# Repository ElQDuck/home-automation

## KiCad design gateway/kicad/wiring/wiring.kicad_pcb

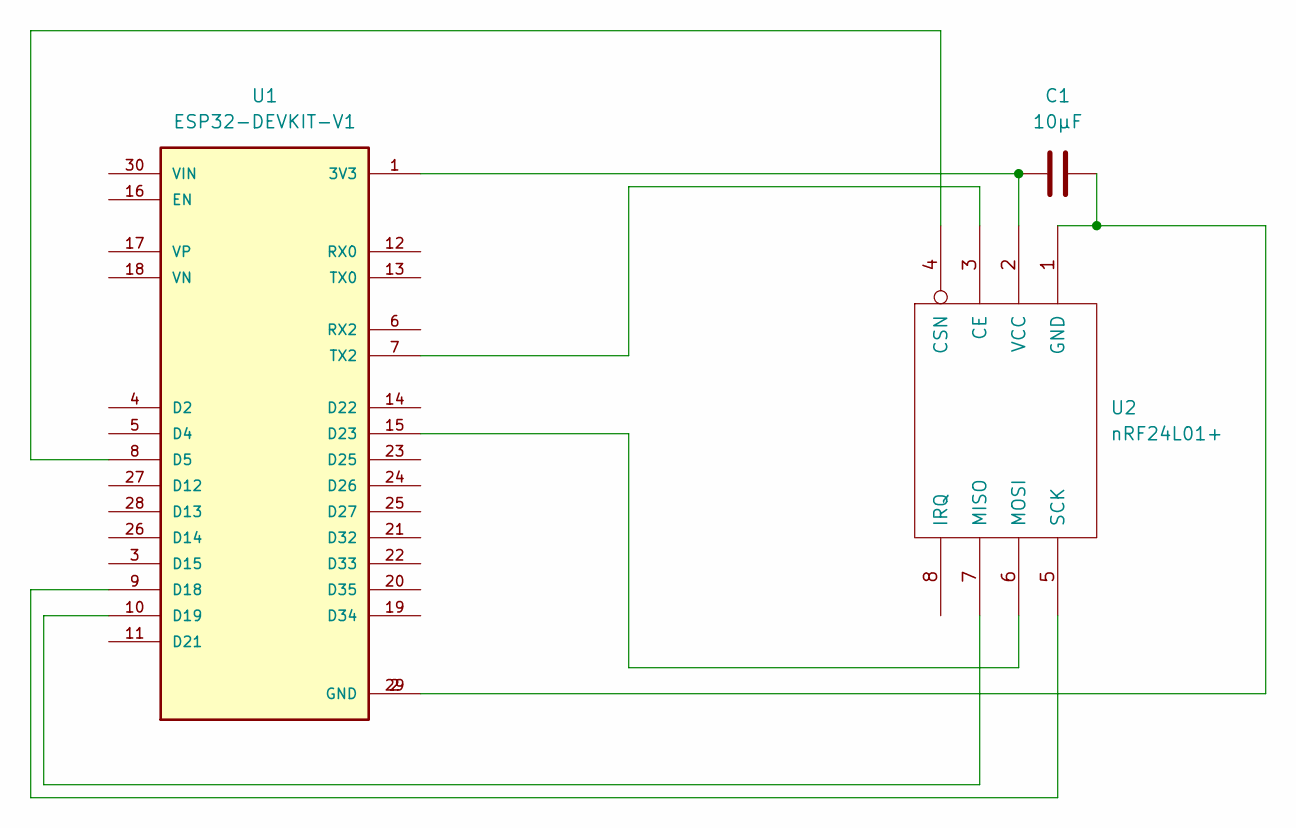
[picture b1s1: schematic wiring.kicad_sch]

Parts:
C1: 10µF; C_Disc_D3.0mm_W1.6mm_P2.50mm
U1: ESP32-DEVKIT-V1; MODULE_ESP32_DEVKIT_V1; PARTREV N/A
U2: nRF24L01+; nRF24L01_Breakout

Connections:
unnamed: C1.1, U1.1 (3V3), U2.2 (VCC)
unnamed: U1.10 (D19), U2.7 (MISO)
unnamed: U1.15 (D23), U2.6 (MOSI)
unnamed: C1.2, U1.2 (GND), U1.29 (GND), U2.1 (GND)
unnamed: U1.7 (TX2), U2.3 (CE)
unnamed: U1.8 (D5), U2.4 (CSN)
unnamed: U1.9 (D18), U2.5 (SCK)

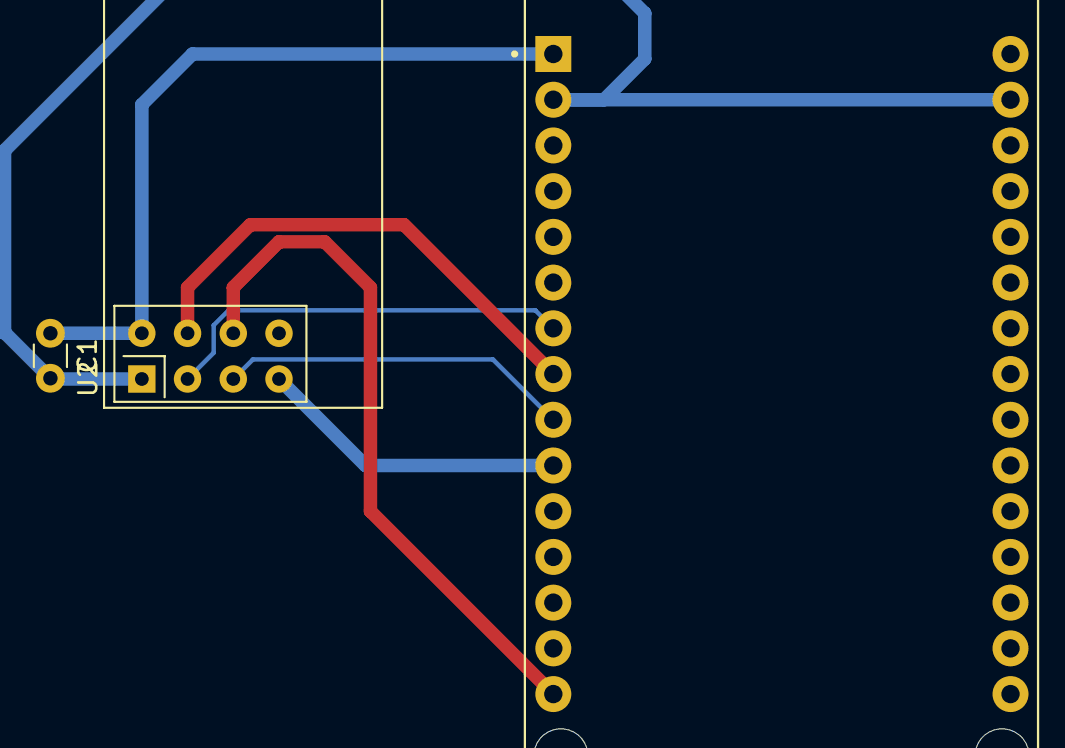
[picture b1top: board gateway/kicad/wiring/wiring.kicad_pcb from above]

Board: 2 copper layers, 3 parts (0 on the bottom side), 7 nets.

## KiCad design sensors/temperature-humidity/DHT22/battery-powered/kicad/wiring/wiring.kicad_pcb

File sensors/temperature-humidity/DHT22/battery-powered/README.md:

# A battery powered temperature and humidity sensor
Used Hardware
- Sensor: [DHT22]()
- Microcontroller: [Arduino Pro Mini ATmega328 3.3V 8MHz ]()
- Wifi connection: [NRF24L01 2.4GHz]()
- Battery: 2 x AA-Battery
- Programmer: [FTDI USB to TTL Serial Adapter](https://www.mikrocontroller.net/topic/435491)
    - [Drivers](https://ftdichip.com/drivers/)

## Development Environment Setup
1. Install [Visual Studio Code](https://code.visualstudio.com/download)
2. Install [PlatformIO IDE](https://marketplace.visualstudio.com/items?itemName=platformio.platformio-ide)
    1. C++ libraries:
        1. [DHT](https://github.com/markruys/arduino-DHT)
        2. [rapidjson](https://github.com/Tencent/rapidjson)
        3. [ArduinoUniqueID](https://github.com/ricaun/ArduinoUniqueID)
        4. [MySensors](https://github.com/mysensors/MySensors/tree/master)
        5. [RF24](https://github.com/nRF24/RF24)
        6. [RF24Network](https://github.com/nRF24/RF24Network)
        7. [arduino-mqtt](https://github.com/256dpi/arduino-mqtt/)
        8. [Low-Power](https://github.com/rocketscream/Low-Power)
        9. [RF24Mesh](https://github.com/nRF24/RF24Mesh)
        10. [RF24Ethernet](https://github.com/nRF24/RF24Ethernet)
4. Install [KiCad]()
    1. [Arduino Libary](https://github.com/Duckle29/kicad-libraries)
    2. [NRF24L01 Library](https://github.com/myelin/myelin-kicad-libraries)
    3. [DHT22 Sensor Library](https://github.com/skorokithakis/kicad-lib.git)
    
    [//]: # (TODO: Move libs into repository)
    
5. (Alternative) install [FreeCAD]()

## Wiring

## Programming
!Attention! After pressing the upload button press the reset button on the Arduino pro mini.

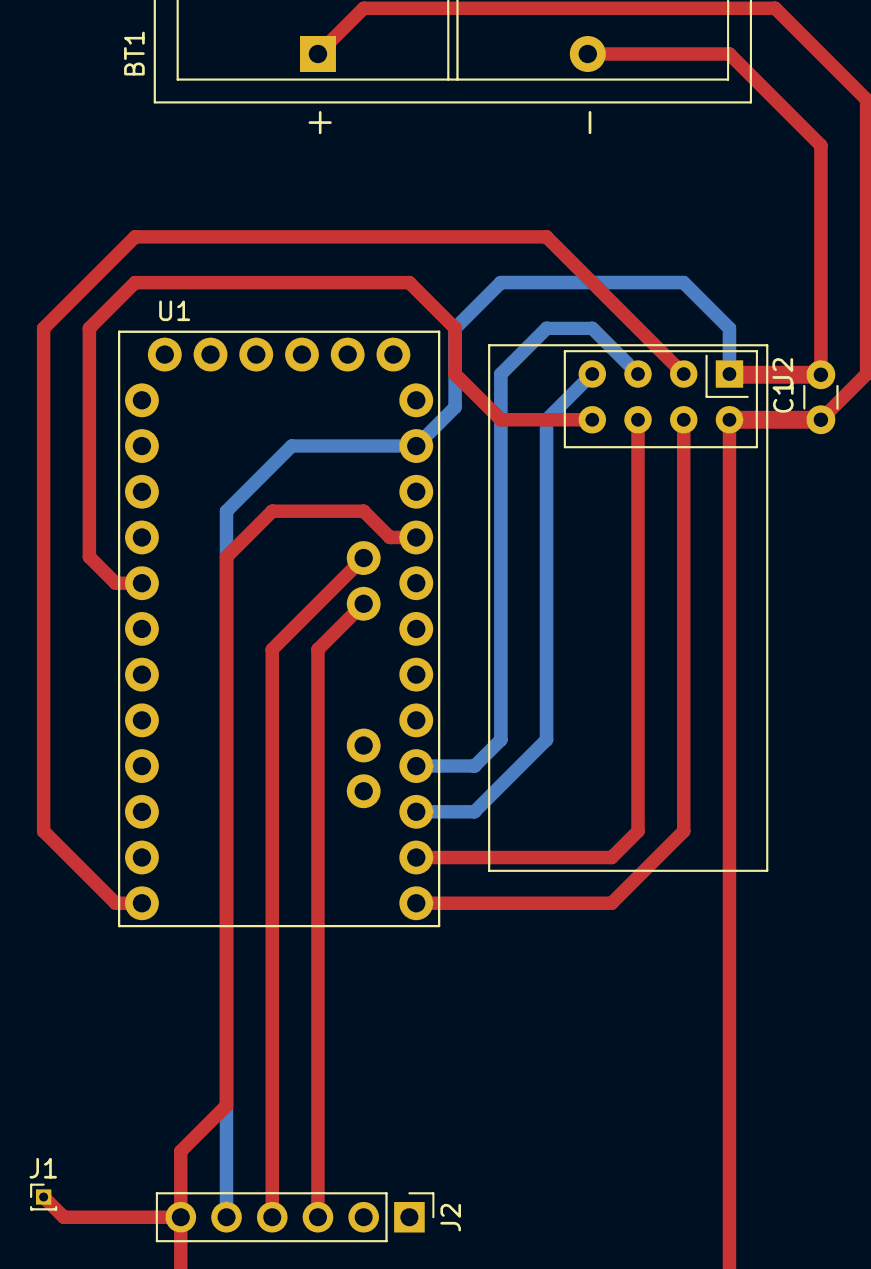
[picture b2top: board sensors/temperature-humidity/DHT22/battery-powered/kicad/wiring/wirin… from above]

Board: 2 copper layers, 6 parts (0 on the bottom side), 11 nets.

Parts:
BT1: 2x1,5V; BatteryHolder_Keystone_2462_2xAA
C1: 10µF; C_Disc_D3.0mm_W1.6mm_P2.50mm
J1: Conn_01x01_Male; PinHeader_1x01_P1.00mm_Vertical
J2: BME280; PinHeader_1x06_P2.54mm_Vertical
U1: ARDUINO_PRO_MINI; MODULE_ARDUINO_PRO_MINI
U2: nRF24L01+; nRF24L01_Breakout

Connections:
GND: BT1.2 (-), C1.2, J2.5, U1.JP6_2 (GND_1), U2.1 (GND)
unnamed: U1.JP1_5 (GND), U1.JP1_6 (GND)
unnamed: J2.3, U1.JP2_1 (A4)
unnamed: J2.4, U1.JP2_2 (A5)
unnamed: BT1.1 (+), C1.1, J1.1, J2.6, U1.JP6_4 (VCC_1), U2.2 (VCC)
unnamed: U1.JP6_9 (SCK), U2.5 (SCK)
unnamed: U1.JP6_10 (MISO), U2.7 (MISO)
unnamed: U1.JP6_11 (MOSI), U2.6 (MOSI)
unnamed: U1.JP6_12 (D10), U2.4 (CSN)
unnamed: U1.JP7_1 (D9), U2.3 (CE)
unnamed: U1.JP7_8 (D2), U2.8 (IRQ)

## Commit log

2022-02-22 feat: adding readme
2022-02-22 feat: new kicad project
2022-02-22 feat: adding library
2022-02-24 feat: using platform io
2022-02-25 feat: add platform io project
2022-02-25 feat: adding libraries to kikad
2022-02-25 feat: adding schematics
2022-02-25 feat: adding mqtt deployment
2022-02-25 refactor: minor changes
2022-02-26 feat: add openhab yaml
2022-03-02 feat: adding first sketch
2022-03-26 feat: adding json creation and arduino id
2022-03-26 feat: adding battery voltage measurement
2022-03-26 feat: using better method to measure voltage
2022-03-28 feat: add library and code
2022-03-28 feat: readme
2022-03-28 feat: new project
2022-03-28 feat: renaming and adding lib
2022-03-28 feat: faster serial
2022-03-29 feat: adding rf comunication
2022-03-30 feat: adding wifi manager
2022-04-02 feat: adding logging
2022-04-02 feat: adding input text handling
2022-04-05 feat: using library for message sending
2022-04-10 feat: finaly sending string over air
2022-04-10 refactor: renamin folders
2022-04-18 refactor: clean up code
2022-04-18 feat: adding sleep mode
2022-04-19 feat: use more libs
2022-04-19 feat: using pubsubclient
2022-04-19 feat: test publish to mqtt
2022-04-22 feat: adding mqtt connection status read
2022-04-23 feat: adding bme280 sensor
2022-04-26 feat: optimizing code
2022-05-03 feat: sending complete json
2022-05-03 refactor: debug var as const
2022-05-07 refactor: cleanup
2022-05-18 feat: adding json lib
2022-05-29 feat: sending first data to mqtt
2022-05-29 feat: adding all sensor values to mqtt
2022-06-04 feat: better wiring
2022-06-05 refactor: move to right directory
2022-06-05 feat: add libs and gitignore
2022-06-05 feat: wiring for gateway
2022-06-12 fix: use sender address as id
